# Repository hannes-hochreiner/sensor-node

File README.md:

# Sensor Node
A simple wireless sensor node.

## Requirements
  * measurements of temperature and humidity
  * wireless operation
  * cost of parts for one node <= 30 EUR
  * one measurement per minute, if a change larger than 10 % is observed; otherwise, one measurement every 10 minutes

  * MCU architecture needs to be ARM Cortex M0 (because I was interested in the platform as a replacement for AVR MCUs)
  * no leadless parts (because I was not equiped to solder them)

## Outline
The plan was to just quickly throw together a sensor, an MCU, a wireless module and a battery.

### MCU selection
I choose to go with the EFM32ZG222F32, because it was fairly cheap, low power and seemed to have good documentation.
As a bonus it has AES encryption functions, which makes the radio selection easier.
I also checked out Silicon Labs IDE and quite liked it.

Other candidates where the LPC81/2 (higher power and no AES) and the STM32F03 (no AES).

### Sensor selection
Adafruit Si7021 breakout board.
Seems to be a good sensor, which I could get my hands on for a reasonable price.
My preference would have been to use the sensor without the breakout board, but since it came in a leadless package I needed the breakout board.

### Wireless chip selection
The Si4012, because it is cheap and has very good documentation.

## Details

### Power and decoupling for the EFM32ZG
I found the recommended power and decoupling setup in Silicon Labs' "AN0002 Hardware Design Considerations".
The summary is, VSS go directly to ground, VDD_DREG gets 0.1 µF and 10 µF, DECOUPLE gets 1 µF, IOVDD get 0.1 µF each and one 10 µF, and AVDD get 10 nF each and one 10 µF.

### Power and decoupling for the Si4012
I followed the recommendation of the datasheet.
VDD got 1µF and the power supply for TXM and TXP got an LC filter with 220 nH and 0.5 pF resulting in a band pass of about 480 MHz.

### Power and decoupling for the Si7021
Ground was connected to a GPIO to be able to disable the module when it is not in use.
Decoupling has to be checked.

### External oscillators
I figured that I did not need any external oscillators since the communication on the board worked over I2C (which has a clock signal) and the radio claimed to have an internal oscillator that was precise enough.

### I2C
The three major things to consider with I2C seemed to me to be the addresses that are used, the speed the modules can handle and the pull-ups that are required.

Addresses and speeds are fairly easy to obtain.
A quick look into the datasheets told me the following:

  * Si7021: address: 0b1000000x; speeds: max 400 kHz; does clock strechting over 100 kHz.
  * Si4012: address: 0b1110000x (configurable); speeds: 100 kbps and 400 kbps.

When it comes to the pull-ups, it gets a little bit trickier.
However, I found a lot of documentation on the net explaining how to calculate the suitable intervals.
I used the Texas Instruments Application Report SLVA689 from February 2015.

I started out by calculating the maximum value, which depends essentially on the bus capacitance and the speed.
The bus capacitance is the capacitance of the pins plus that of the trace.
One problem I had was that I was not able to find any values for the capacitance the pins of my chosen chips added to the bus in the datasheets.
After investigating the topic for a while, I concluded that 10 pF should be a fairly conservative assumption.

To calculate the trace capacitance, I used the online calculator of the [Missouri University of Science and Technology](http://emclab.mst.edu/pcbtlc2/microstrip/).
The required parameters I obtained from OSHPark ([2 Layer Prototype](http://docs.oshpark.com/services/two-layer/), [2 Layer 2oz 0.8mm](http://docs.oshpark.com/services/two-layer-hhdc/)).
I assumed a trace width of 10 mils.

  * <0.5 pF / cm for the 2 layer prototype service
  * <0.6 pF / cm for the 2 layer 2 oz 0.8mm service

Given that there were three ICs on the bus and that the trace length would be smaller 3 cm, I estimated that the bus capacitance should be smaller 35 pF.
From that, I calculated the maximum resistance for the pull-ups at different speeds.

  * 33 kOhm for 100 kHz
  * 10 kOhm for 400 kHz

I tried calculating the minimum values for the pull-up resistors for all ICs.
However, only the datasheet of the Si7021 provided the required values.
The minimum resistance for the Si7021 was 1.1 kOhm.
I took this value as a representative value of all involved ICs.

In the end, I decided to go with 400 kHz transmission speed using 10 kOhm pull-ups.
One thing to note is that the Si4012 had a 50 kOhm integrated pull-up.
Hence the 10 kOhm would effectively only be about 8.5 kOhm.
I figured that this should give me an additional margin, but it was also something I had to consider at the time of calculating the battery life.

### Antenna
I chose to go with a loop antenna, because I have had problems with dipole antennas in the past.
Often the dipole antennas worked fine on the breadboard, but in the finished product the performed considerable worse.
Since I don't have the equipment to do an in-depth analysis, I left with (more or less educated) guesses.
I attributed the drop in antenna performance to the fact that the breadboard was acting as a ground plane.
In the finished sensor, there was no comparable ground plane and therefore the performance was worse.
As I was trying to get the sensors as compact as possible and I did not want to go higher frequencies, I thought that loop antennas were my best shot.
They are relatively small, don't need a ground plane and can be printed on the PCB.

To tune the antenna size, I wrote a small program.
I based my calculations of the loop inductance on a NIST paper ([E.B. Rosa "The self and mutual inductances of linear conductors," Bulletin of the Bureau of Standards, vol. 4, no. 2, p. 301](http://nvlpubs.nist.gov/nistpubs/bulletin/04/nbsbulletinv4n2p301_A2b.pdf)).
This paper gave a closed form equation for the conductance of a rectangular loop, while in the application notes I could only find conversions to equivalent circular structures.
The results were within 5 % of the approximations found in the application notes.

I calculated the size of the feed loop based on two different application notes.
[Microchip AN831](http://ww1.microchip.com/downloads/en/AppNotes/00831b.pdf) seemed to use a simpler approach basically neglecting the effect of the PCB.
[Silicon Labs AN639](http://www.silabs.com/Support%20Documents/TechnicalDocs/AN639.pdf) took the effect of the PCB into account, but used empirical factors to do so.
Although I thought it would be good to take the effect of the PCB into account, I wasn't quite sure the assumptions for the empirical factors help for my design.

With both approximations, I obtained about -8 dB for the estimated gain.
The length of the feed loop came out quite differently (10.5 mm to 16.1 mm).
In the end I decided to go with 14 mm, because I figured that it would be easier to compensate for a slightly to large loop than for a slightly to small loop.

### SWD
I added a 10 pin Cortex Debug connector based on the [ARM recommendation](http://infocenter.arm.com/help/topic/com.arm.doc.faqs/attached/13634/cortex_debug_connectors.pdf).

### BOM

A detailed bill of materials can be found on a [sub-page](bom.md).

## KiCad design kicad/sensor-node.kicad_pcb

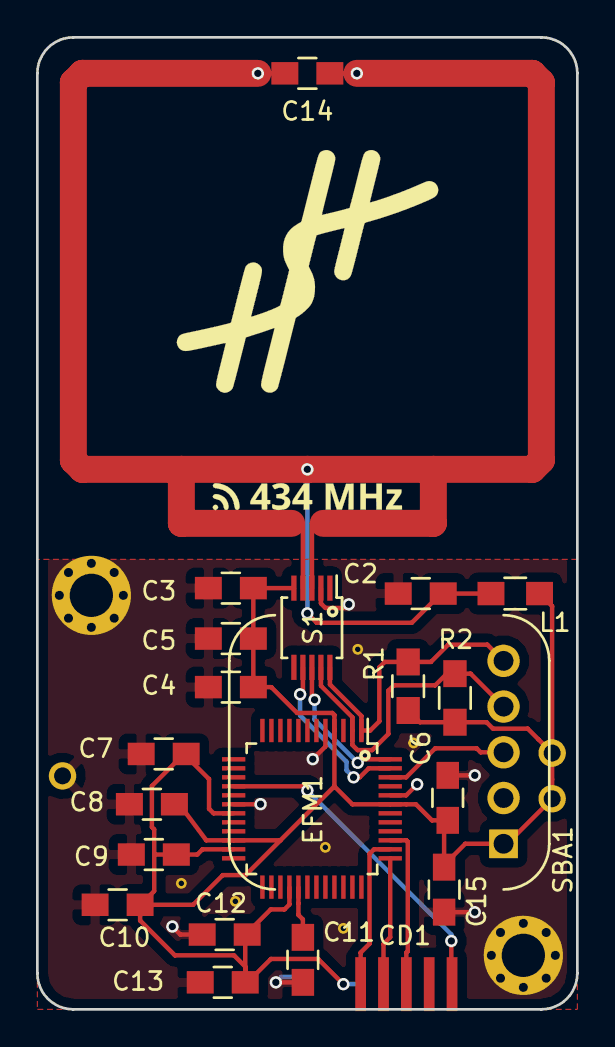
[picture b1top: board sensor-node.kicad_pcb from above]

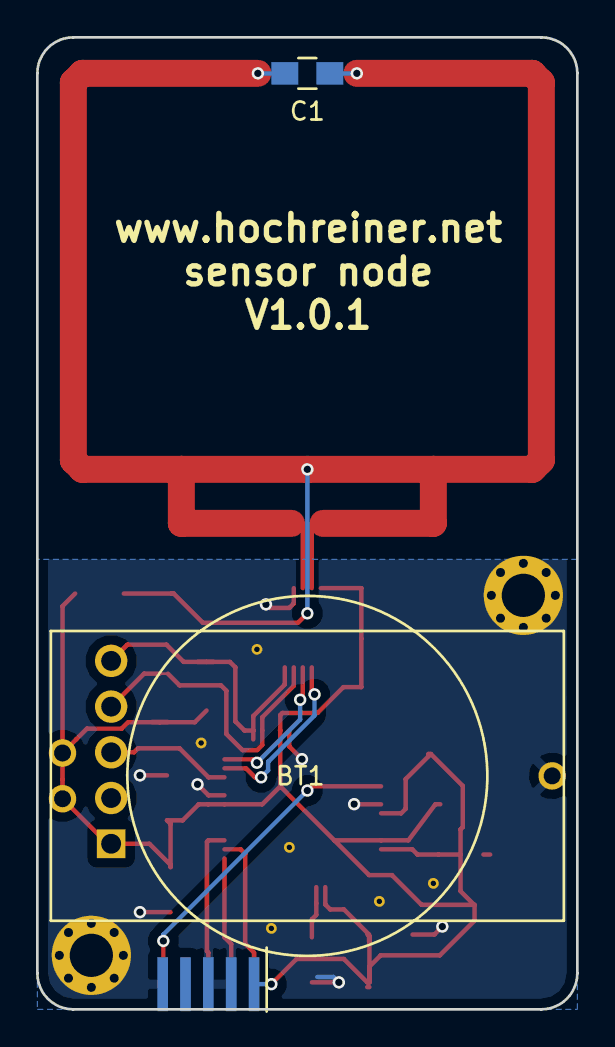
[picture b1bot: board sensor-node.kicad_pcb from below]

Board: 2 copper layers, 30.0 x 54.0 mm, 23 parts (2 on the bottom side), 13 nets.

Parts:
BT1: CR2032Holder; HU2032-LF
C1, C14: 1pF; C_0805_HandSoldering
C2: 0.5pF; C_0805_HandSoldering
C3, C11: 1µF; C_0805_HandSoldering
C4, C6, C8, C12: 0.1µF; C_0805_HandSoldering
C5, C10, C13, C15: 10µF; C_0805_HandSoldering
C7, C9: 10nF; C_0805_HandSoldering
CD1: CortexDebug; CORTEX-DEBUG-EDGE
EFM1: EFM32ZG222; TQFP-48_7x7mm_Pitch0.5mm
L1: 220nH; R_0805_HandSoldering
R1, R2: 10k; R_0805_HandSoldering
S1: Si4012; MSOP-10_3x3mm_Pitch0.5mm
SBA1: Si7021-BA; Si7021BA

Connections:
+3V3: BT1.1, C3.1, C4.1, C5.1, C6.2, C7.1, C8.1, C9.1, C10.1, C12.1, C13.1, C15.2, CD1.1, EFM1.4, EFM1.19, EFM1.22, EFM1.23, EFM1.28, EFM1.43, L1.1, R1.2, R2.2, S1.5, SBA1.1
/RAD_ENABLE: EFM1.48, S1.8
/RAD_INT: EFM1.47, S1.7
/SCL: EFM1.2, R2.1, S1.9, SBA1.4
/SDA: EFM1.1, R1.1, S1.10, SBA1.5
/SWCLK: CD1.4, EFM1.37
/SWDIO: CD1.2, EFM1.38
/SWO: CD1.6, EFM1.39
/~RESET: CD1.10, EFM1.16
/~SEN_ENABLE: EFM1.46, SBA1.3
GND: BT1.2, C2.2, C3.2, C4.2, C5.2, C6.1, C7.2, C8.2, C9.2, C10.2, C11.1, C12.2, C13.2, C15.1, CD1.3, CD1.5, CD1.9, EFM1.5, EFM1.18, EFM1.44, S1.2
unnamed: C1.1, C1.2, C2.1, C14.1, C14.2, L1.2, S1.3, S1.4
unnamed: C11.2, EFM1.29

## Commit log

2017-01-09 started documentation
2017-01-10 updated the sensor selection
2017-01-12 started circuit diagram
2017-01-14 added basic wiring for the MCU and the radio
2017-01-14 added sensor
2017-01-14 added I2C design
2017-01-19 updated pull-up values in the diagram
2017-01-21 added debug connector
2017-01-21 fixed some minor problems
2017-01-21 added some annotation
2017-01-21 started working on an antenna design tool
2017-01-21 added function to calculate the secondary loop length
2017-01-21 added more functions
2017-01-22 added clarification
2017-01-22 added capacitance calculation
2017-01-22 added the velocity factor for the calculation of the radiation resistance
2017-01-22 updated the calculation of the trace resistance
2017-01-22 refactoring to eliminate module constants
2017-01-22 started design calculations
2017-01-22 added esr calculation
2017-01-22 improved calculations
2017-01-22 switched formatting
2017-01-22 switched tests to use d3-format
2017-01-24 started board layout
2017-01-24 started routing
2017-01-24 extended bom
2017-01-25 added custom footprints
2017-01-26 continued routing
2017-01-28 automated bom creation and moved it to a separate page
2017-01-28 added link to bom
2017-01-28 removed led
2017-01-28 removed uart
2017-01-28 updated bom
2017-01-29 added components that are not in the circuit diagram
2017-01-29 added missing components
2017-01-29 added order cost table
2017-01-31 minor routing changes
2017-02-01 improved routing
2017-02-02 more routing
2017-02-03 added mounting holes and custom footprint for sensor module
2017-02-04 added board outline
2017-02-04 more rounting and antenna planning
2017-02-04 recalculated antenna
2017-02-04 redrew antenna
2017-02-05 adde model for the battery holder
2017-02-05 added simple 3d model for the break out board
2017-02-06 switched supplier
2017-02-07 moved cortex debug connector futher to the right
2017-02-07 moved mounting hole and battery slightliy down
2017-02-07 moved inductivity up
2017-02-09 check i2c connections
2017-02-09 rounded antenna edges
2017-02-11 refined feed loop size
2017-02-11 added a decoupling capacitor
2017-02-11 improved silk screen decoration
2017-02-11 updated design rules to OSH Park settings
2017-02-18 added 3D model of the shrouded header
2017-02-25 added more description of the antenna choice
2017-03-12 added openocd configuration
2017-04-08 added a first test program
2017-04-08 added a project log entry
2017-04-08 added a page for lessons learned
2017-04-09 added openocd config
2017-04-09 added more documentation on flashing the chip
2017-04-09 added new project log
2017-04-09 fixed a typo
2017-04-14 added a new project log entry
2017-04-15 modified firmware to include sensor
2017-04-17 added another project log
2017-04-17 fixed battery model name
2017-04-17 updated the kicad project
2017-04-17 fixed Si7012 pin assignment
2017-04-17 minor fix of the board
2017-04-17 increased version number of the board
2017-04-17 added logo, mounting, and stitching vias
2017-04-18 improved firmware
2017-04-18 returned mounting hole to former position
2017-04-18 added additional pin 1 indicators for ICs
2017-04-22 updated pcb
2017-04-22 added project log for new pcb version
2017-04-23 added a lesson learned
2017-05-13 added project log
